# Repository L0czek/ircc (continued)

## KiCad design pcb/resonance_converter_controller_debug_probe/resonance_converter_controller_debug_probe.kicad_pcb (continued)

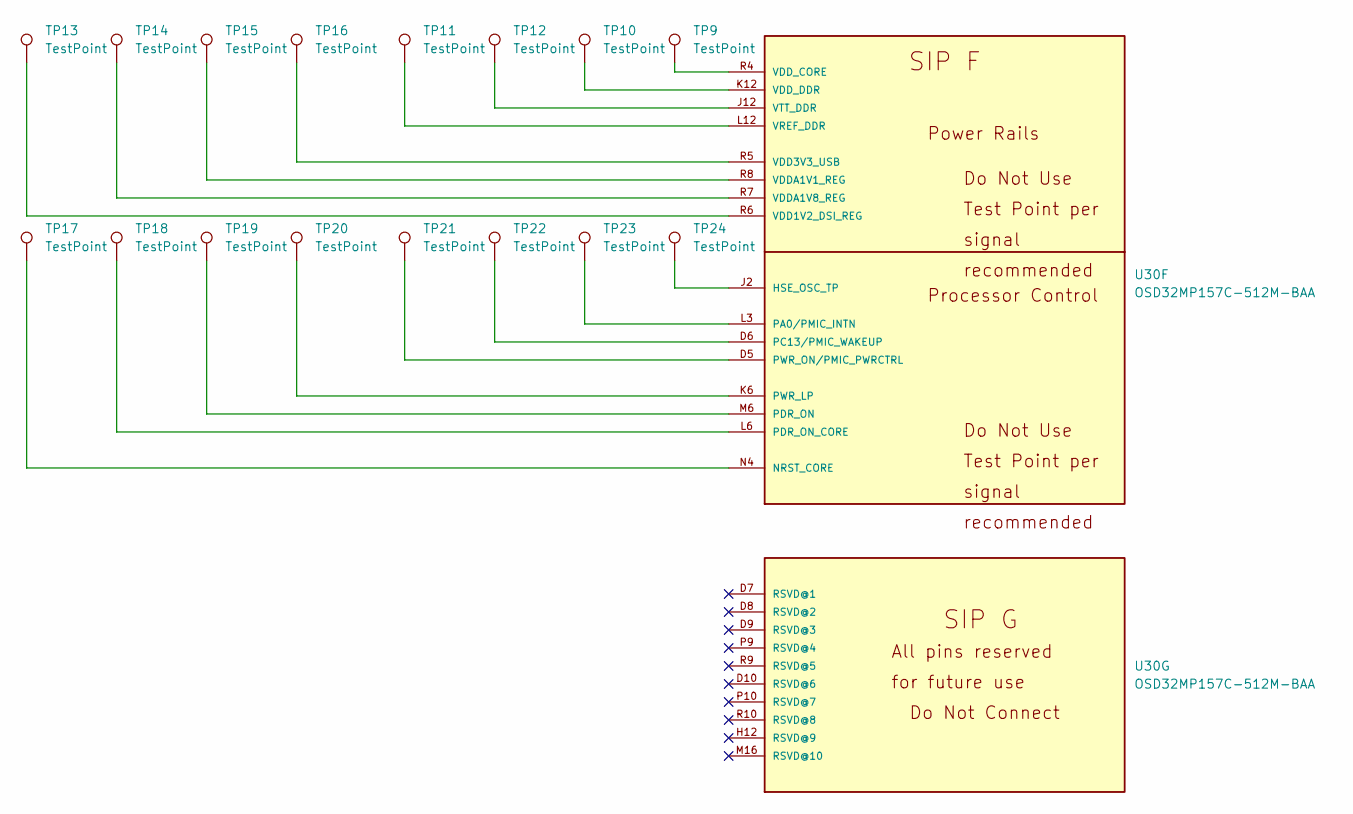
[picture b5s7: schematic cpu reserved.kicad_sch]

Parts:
TP9, TP10, TP11, TP12, TP13, TP14, TP15, TP16, TP17, TP18, TP19, TP20, TP21, TP22, TP23, TP24: TestPoint; TestPoint_Pad_D1.0mm
U30: OSD32MP157C-512M-BAA; OSD32MP15X-BGA-324

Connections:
unnamed: TP24.1, U30.J2 (HSE_OSC_TP)
unnamed: TP17.1, U30.N4 (NRST_CORE)
unnamed: TP23.1, U30.L3 (PA0/PMIC_INTN)
unnamed: TP22.1, U30.D6 (PC13/PMIC_WAKEUP)
unnamed: TP19.1, U30.M6 (PDR_ON)
unnamed: TP18.1, U30.L6 (PDR_ON_CORE)
unnamed: TP20.1, U30.K6 (PWR_LP)
unnamed: TP21.1, U30.D5 (PWR_ON/PMIC_PWRCTRL)
unnamed: TP13.1, U30.R6 (VDD1V2_DSI_REG)
unnamed: TP16.1, U30.R5 (VDD3V3_USB)
unnamed: TP15.1, U30.R8 (VDDA1V1_REG)
unnamed: TP14.1, U30.R7 (VDDA1V8_REG)
unnamed: TP9.1, U30.R4 (VDD_CORE)
unnamed: TP10.1, U30.K12 (VDD_DDR)
unnamed: TP11.1, U30.L12 (VREF_DDR)
unnamed: TP12.1, U30.J12 (VTT_DDR)

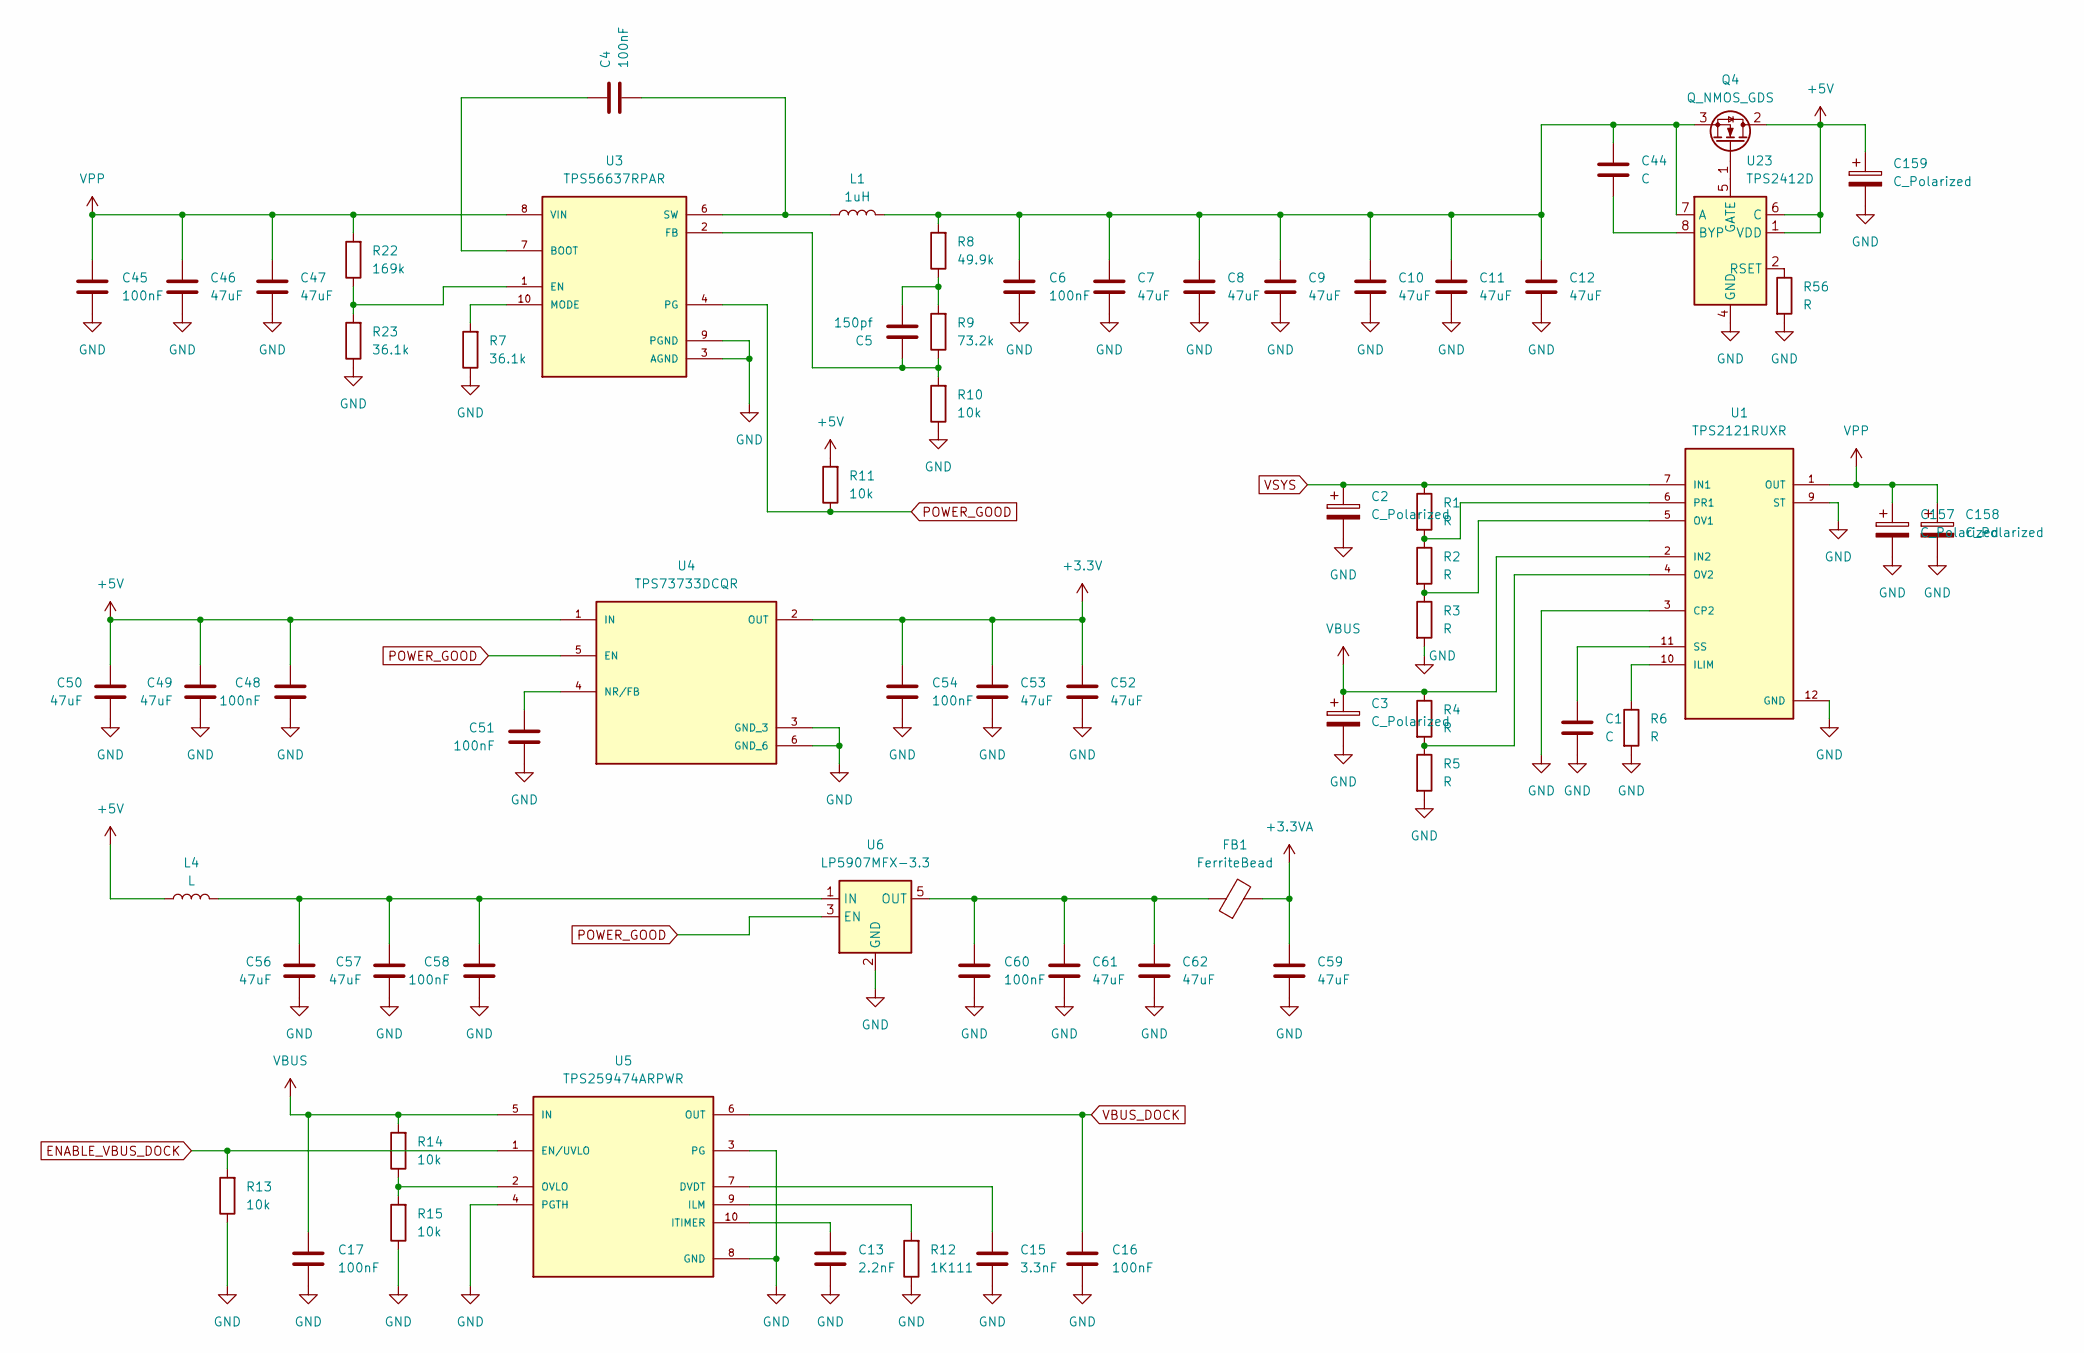
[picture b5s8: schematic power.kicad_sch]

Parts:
C1: C; C_0402_1005Metric
C2, C3, C157, C158, C159: C_Polarized; C_2220_5750Metric
C4, C6, C16, C17, C45, C48, C51, C54, C58, C60: 100nF; C_0402_1005Metric
C5: 150pf; C_0402_1005Metric
C7, C8, C9, C10, C11, C12, C46, C47, C49, C50, C52, C53, C56, C57, C59, C61, C62: 47uF; C_1206_3216Metric
C13: 2.2nF; C_0402_1005Metric
C15: 3.3nF; C_0402_1005Metric
C44: C; C_0805_2012Metric
FB1: FerriteBead; L_0805_2012Metric
L1: 1uH; L_10.4x10.4_H4.8
L4: L; L_1812_4532Metric
Q4: Q_NMOS_GDS; TO-252-2
R1, R2, R3, R4, R5, R6, R56: R; R_0402_1005Metric
R7, R23: 36.1k; R_0402_1005Metric
R8: 49.9k; R_0402_1005Metric
R9: 73.2k; R_0402_1005Metric
R10, R11, R13, R14, R15: 10k; R_0402_1005Metric
R12: 1K111; R_0402_1005Metric
R22: 169k; R_0402_1005Metric
U1: TPS2121RUXR; IC_TPS2121RUXR
U3: TPS56637RPAR; CONV_TPS56637RPAR; PARTREV A
U4: TPS73733DCQR; IC_TPS73733DCQR; PARTREV R
U5: TPS259474ARPWR; IC_TPS259474ARPWR; PARTREV A
U6: LP5907MFX-3.3; SOT-23-5
U23: TPS2412D; TSSOP-8_4.4x3mm_P0.65mm

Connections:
+3.3V: C52.1, C53.1, C54.1, U4.2 (OUT); also elsewhere on the board
+3.3VA: C59.1, FB1.2; also elsewhere on the board
+5V: C48.1, C49.1, C50.1, C159.1, L4.1, Q4.2 (D), R11.2, U4.1 (IN), U23.1 (VDD), U23.6 (C); also elsewhere on the board
ENABLE_VBUS_DOCK: R13.2, U5.1 (EN/UVLO)
GND: C1.2, C2.2, C3.2, C6.2, C7.2, C8.2, C9.2, C10.2, C11.2, C12.2, C13.2, C15.2, C16.2, C17.2, C45.2, C46.2, C47.2, C48.2, C49.2, C50.2, C51.2, C52.2, C53.2, C54.2, C56.2, C57.2, C58.2, C59.2, C60.2, C61.2, C62.2, C157.2, C158.2, C159.2, R3.2, R5.2, R6.2, R7.1, R10.1, R12.1, R13.1, R15.1, R23.1, R56.2, U1.3 (CP2), U1.9 (ST), U1.12 (GND), U3.3 (AGND), U3.9 (PGND), U4.3 (GND_3), U4.6 (GND_6), U5.3 (PG), U5.4 (PGTH), U5.8 (GND), U6.2 (GND), U23.3 (GND), U23.4 (GND); also elsewhere on the board
unnamed: C5.2, R8.1, R9.2
unnamed: Q4.1 (G), U23.5 (GATE)
unnamed: C6.1, C7.1, C8.1, C9.1, C10.1, C11.1, C12.1, C44.1, L1.2, Q4.3 (S), R8.2, U23.7 (A)
unnamed: R6.1, U1.10 (ILIM)
unnamed: R2.2, R3.1, U1.5 (OV1)
unnamed: R4.2, R5.1, U1.4 (OV2)
unnamed: R1.2, R2.1, U1.6 (PR1)
unnamed: C1.1, U1.11 (SS)
unnamed: C4.1, U3.7 (BOOT)
unnamed: R22.1, R23.2, U3.1 (EN)
unnamed: C5.1, R9.1, R10.2, U3.2 (FB)
unnamed: R7.2, U3.10 (MODE)
unnamed: C4.2, L1.1, U3.6 (SW)
unnamed: C51.1, U4.4 (NR/FB)
unnamed: C15.1, U5.7 (DVDT)
unnamed: R12.2, U5.9 (ILM)
unnamed: C13.1, U5.10 (ITIMER)
unnamed: R14.1, R15.2, U5.2 (OVLO)
unnamed: C56.1, C57.1, C58.1, L4.2, U6.1 (IN)
unnamed: C60.1, C61.1, C62.1, FB1.1, U6.5 (OUT)
unnamed: C44.2, U23.8 (BYP)
unnamed: R56.1, U23.2 (RSET)
POWER_GOOD: R11.1, U3.4 (PG), U4.5 (EN), U6.3 (EN)
VBUS: C3.1, C17.1, R4.1, R14.2, U1.2 (IN2), U1.2_1 (IN2), U5.5 (IN); also elsewhere on the board
VBUS_DOCK: C16.1, U5.6 (OUT); also elsewhere on the board
VPP: C45.1, C46.1, C47.1, C157.1, C158.1, R22.2, U1.1 (OUT), U1.1_1 (OUT), U1.8 (OUT), U1.8_1 (OUT), U3.8 (VIN)
VSYS: C2.1, R1.1, U1.7 (IN1), U1.7_1 (IN1); also elsewhere on the board

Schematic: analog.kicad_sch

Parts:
C30, C68, C69, C70, C71, C98, C103: 100nF; C_0402_1005Metric
D3, D7, D10, D11, D12, D13, D37: ESD9B3.3ST5G; D_SOD-923
R38, R43, R76, R78: 10K; R_0402_1005Metric
U9, U10, U11, U27: INA169; SOT-23-5
U12, U16: MCP4441-xxxx-ST; TSSOP-20_4.4x6.5mm_P0.65mm
U28: OPA356xxDBV; SOT-23-5

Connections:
+3.3V: C30.1, C103.1, U12.4 (HVC/A0), U12.15 (~RESET), U12.16 (A1), U12.17 (VDD), U16.4 (HVC/A0), U16.15 (~RESET), U16.16 (A1), U16.17 (VDD); also elsewhere on the board
+3.3VA: C68.2, C69.2, C70.2, C71.2, C98.1, U9.5 (V+), U10.5 (V+), U11.5 (V+), U27.5 (V+), U28.5 (V+); also elsewhere on the board
AUX_ADC: D3.2 (A2), R43.2; also elsewhere on the board
DAC_OUT: D37.2 (A2), R78.2; also elsewhere on the board
GND: C30.2, C68.1, C69.1, C70.1, C71.1, C98.2, C103.2, D3.1 (A1), D7.1 (A1), D10.1 (A1), D11.1 (A1), D12.1 (A1), D13.1 (A1), D37.1 (A1), R38.1, R43.1, R78.1, U9.2 (GND), U9.4 (-), U10.2 (GND), U10.4 (-), U11.2 (GND), U11.4 (-), U12.2 (P3W), U12.3 (P3B), U12.7 (VSS), U12.8 (P1B), U12.9 (P1W), U12.12 (P0W), U12.13 (P0B), U12.18 (P2B), U12.19 (P2W), U16.1 (P3A), U16.7 (VSS), U16.12 (P0W), U16.13 (P0B), U27.2 (GND), U27.4 (-), U28.2 (V-); also elsewhere on the board
I2C_INT_SCL: U12.5 (SCL), U16.5 (SCL); also elsewhere on the board
I2C_INT_SDA: U12.6 (SDA), U16.6 (SDA); also elsewhere on the board
ISENSE_1: D7.2 (A2), U9.3 (+); also elsewhere on the board
ISENSE_1_OUT: U9.1, U12.20 (P2A)
ISENSE_2: D10.2 (A2), U27.3 (+); also elsewhere on the board
ISENSE_2_OUT: U12.1 (P3A), U27.1
ISENSE_3: D11.2 (A2), U10.3 (+); also elsewhere on the board
ISENSE_3_OUT: U10.1, U12.10 (P1A)
ISENSE_4: D12.2 (A2), U11.3 (+); also elsewhere on the board
ISENSE_4_OUT: U11.1, U12.11 (P0A)
unnamed: R76.1, U16.11 (P0A), U28.4 (-)
VSENSE_IN: D13.2 (A2), R38.2, U28.3 (+); also elsewhere on the board
VSENSE_OUT: R76.2, U28.1

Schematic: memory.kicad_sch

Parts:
C105, C106, C108: 100nF; C_0402_1005Metric
C107: 10uF; C_1206_3216Metric
C109: 100uF; C_1206_3216Metric
J9, J10: Micro_SD_Card_Det2; microSD_HC_Hirose_DM3BT-DSF-PEJS
R67: 0R; R_0402_1005Metric; not fitted
R68: 240K; R_0402_1005Metric
R69: 100K; R_0402_1005Metric
U31: TPS2553DRVR; SON65P200X200X80-7N

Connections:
+3.3V: C105.1, R67.1, R69.2, U31.6 (IN); also elsewhere on the board
GND: C105.2, C106.2, C107.2, C108.2, C109.2, J9.6 (VSS), J9.10 (DET_A), J9.11 (SHIELD), J10.6 (VSS), J10.10 (DET_A), J10.11 (SHIELD), R68.2, U31.5 (GND), U31.7 (EP); also elsewhere on the board
unnamed: C107.1, C108.1, C109.1, J9.4 (VDD), J10.4 (VDD), U31.1 (OUT)
unnamed: C106.1, R69.1, U31.3 (~FAULT), U31.4 (EN)
unnamed: R67.2, R68.1, U31.2 (ILIM)
SD0_CLK: J9.5 (CLK); also elsewhere on the board
SD0_CMD: J9.3 (CMD); also elsewhere on the board
SD0_D0: J9.7 (DAT0); also elsewhere on the board
SD0_D1: J9.8 (DAT1); also elsewhere on the board
SD0_D2: J9.1 (DAT2); also elsewhere on the board
SD0_D3: J9.2 (DAT3/CD); also elsewhere on the board
SD0_DET: J9.9 (DET_B)
SD1_CLK: J10.5 (CLK); also elsewhere on the board
SD1_CMD: J10.3 (CMD); also elsewhere on the board
SD1_D0: J10.7 (DAT0); also elsewhere on the board
SD1_D1: J10.8 (DAT1); also elsewhere on the board
SD1_D2: J10.1 (DAT2); also elsewhere on the board
SD1_D3: J10.2 (DAT3/CD); also elsewhere on the board
SD1_DET: J10.9 (DET_B)

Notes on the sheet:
3.3 bus max 100mA

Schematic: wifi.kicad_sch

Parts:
C110: C_Polarized; CP_EIA-7343-31_Kemet-D
H1: MountingHole_Pad; screw-stud
J11: Bus_M.2_Socket_E; MDTXXXXXX001
R64, R65, R70: 10k; R_0402_1005Metric
R66, R71: 0R; R_0402_1005Metric; not fitted

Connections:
+1V8: R64.1, R65.1; also elsewhere on the board
+3.3V: C110.1, J11.2 (3.3V), J11.4 (3.3V), J11.72 (3.3V), J11.74 (3.3V), R70.1; also elsewhere on the board
BLE_ENABLE: J11.54 (~W_DISABLE2)
BLE_UART_CTS: J11.34 (UART_CTS); also elsewhere on the board
BLE_UART_RTS: J11.36 (UART_RTS); also elsewhere on the board
BLE_UART_RXD: J11.22 (UART_RXD); also elsewhere on the board
BLE_UART_TXD: J11.32 (UART_TXD); also elsewhere on the board
BLE_UART_WAKE: J11.20 (~UART_WAKE), R70.2, R71.2
GND: C110.2, H1.1 (1_1), J11.1 (GND), J11.7 (GND), J11.18 (GND), J11.33 (GND), J11.39 (GND), J11.45 (GND), J11.51 (GND), J11.57 (GND), J11.63 (GND), J11.69 (GND), J11.75 (GND), J11.S1 (GND), J11.S2 (GND); also elsewhere on the board
unnamed: J11.40 (VENDOR_DEFINED), R66.1
unnamed: J11.42 (VENDOR_DEFINED), R71.1
WIFI_ENABLE: J11.56 (~W_DISABLE1)
WIFI_SDIO_CLK: J11.9 (SDIO_CLK); also elsewhere on the board
WIFI_SDIO_CMD: J11.11 (SDIO_CMD); also elsewhere on the board
WIFI_SDIO_D0: J11.13 (SDIO_DATA0); also elsewhere on the board
WIFI_SDIO_D1: J11.15 (SDIO_DATA1); also elsewhere on the board
WIFI_SDIO_D2: J11.17 (SDIO_DATA2); also elsewhere on the board
WIFI_SDIO_D3: J11.19 (SDIO_DATA3); also elsewhere on the board
WIFI_SDIO_RESET: J11.23 (~SDIO_RESET), R65.2
WIFI_SDIO_WAKE: J11.21 (~SDIO_WAKE), R64.2, R66.2
WIFI_SUSCLK: J11.50 (SUSCLK)

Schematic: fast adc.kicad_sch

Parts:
C18, C19, C24, C25, C26, C27, C28, C29, C139, C140, C141, C143, C144: 100nF; C_0402_1005Metric
C20, C21, C22, C23: 10uF; C_1206_3216Metric
C142, C145, C146, C147, C148: 10u; C_0805_2012Metric
D1, D2: ESD9B3.3ST5G; D_SOD-923
L2: L; L_0805_2012Metric
R16, R17, R18, R19, R20, R21, R24, R25, R26, R29, R30, R33, R34, R35, R36, R37, R39, R40: 10K; R_0402_1005Metric
R27, R28, R41, R42: 10R; R_0402_1005Metric
R72: 10k; R_0402_1005Metric
U7: ADC3910D125IRSMT; IC_ADC3910D125IRSMT; PARTREV A
U8, U14: OPA333xxDBV; SOT-23-5
U13, U15: THS4541IRGTT; QFN50P300X300X100-17N
U16: MCP4441-xxxx-ST; TSSOP-20_4.4x6.5mm_P0.65mm
U33: LP5912-1.8DRV; WSON-6-1EP_2x2mm_P0.65mm_EP1x1.6mm_ThermalVias

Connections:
1V8A: C28.1, C29.1, C147.1, C148.1, L2.2, U7.12 (AVDD), U7.13 (AVDD)
+3.3V: C139.1, U7.27 (IOVDD); also elsewhere on the board
+3.3VA: C26.1, C27.1, C140.1, C141.1, C142.1, C143.1, R26.1, R30.1, U8.5 (V+), U13.5 (VS+-2), U13.6 (VS+-3), U13.7 (VS+), U13.8 (VS+-1), U13.12 (PDN), U14.5 (V+), U15.5 (VS+-2), U15.6 (VS+-3), U15.7 (VS+), U15.8 (VS+-1), U15.12 (PDN), U33.4 (EN), U33.6 (IN); also elsewhere on the board
ADC_ALERT: U7.20 (ALERT)
ADC_CLK: U7.8 (CLK)
ADC_D0: U7.4 (D0); also elsewhere on the board
ADC_D1: U7.3 (D1); also elsewhere on the board
ADC_D2: U7.2 (D2); also elsewhere on the board
ADC_D3: U7.1 (D3); also elsewhere on the board
ADC_D4: U7.32 (D4); also elsewhere on the board
ADC_D5: U7.31 (D5); also elsewhere on the board
ADC_D6: U7.26 (D6); also elsewhere on the board
ADC_D7: U7.25 (D7); also elsewhere on the board
ADC_D8: U7.24 (D8); also elsewhere on the board
ADC_D9: U7.23 (D9); also elsewhere on the board
ADC_D10: U7.22 (D10); also elsewhere on the board
ADC_D11: U7.21 (D11); also elsewhere on the board
ADC_DCLK: U7.30 (DCLK); also elsewhere on the board
ADC_OEN: U7.6 (~OEN/PD)
ADC_RESET: U7.9 (RESET)
ADC_SCLK: U7.18 (SCLK); also elsewhere on the board
ADC_SDIO: U7.19 (SDIO); also elsewhere on the board
ADC_SS: U7.16 (~SEN); also elsewhere on the board
GND: C18.1, C21.1, C22.1, C24.1, C26.2, C27.2, C28.2, C29.2, C139.2, C140.2, C141.2, C142.2, C143.2, C144.2, C145.2, C146.2, C147.2, C148.2, D1.1 (A1), D2.1 (A1), R24.1, R25.2, R29.1, R33.2, U7.17 (VREF), U7.28 (DGND), U7.33 (GND), U8.2 (V-), U13.13 (VS--2), U13.14 (VS--3), U13.15 (VS-), U13.16 (VS--1), U14.2 (V-), U15.13 (VS--2), U15.14 (VS--3), U15.15 (VS-), U15.16 (VS--1), U33.5 (GND), U33.7 (EP); also elsewhere on the board
unnamed: C18.2, R17.2
unnamed: C19.1, R18.2
unnamed: C19.2, R21.1, U8.1
unnamed: C20.1, R20.2
unnamed: C23.1, R34.2
unnamed: C24.2, R36.2
unnamed: C25.1, R37.2
unnamed: C25.2, R35.1, U14.1
unnamed: R28.1, U7.11 (INAM)
unnamed: R27.1, U7.10 (INAP)
unnamed: R42.1, U7.15 (INBM/NC)
unnamed: R41.1, U7.14 (INBP/NC)
unnamed: C21.2, R25.1, R26.2, U8.3 (+)
unnamed: R19.1, U13.4 (FB+)
unnamed: R16.1, U13.1 (FB-)
unnamed: R16.2, R17.1, U13.2 (IN+)
unnamed: R18.1, R19.2, U13.3 (IN-)
unnamed: R27.2, U13.10 (OUT+)
unnamed: R28.2, U13.11 (OUT-)
unnamed: C22.2, R30.2, R33.1, U14.3 (+)
unnamed: U14.4 (-), U16.19 (P2W)
unnamed: R40.1, U15.4 (FB+)
unnamed: R39.1, U15.1 (FB-)
unnamed: R36.1, R39.2, U15.2 (IN+)
unnamed: R37.1, R40.2, U15.3 (IN-)
unnamed: R41.2, U15.10 (OUT+)
unnamed: R42.2, U15.11 (OUT-)
unnamed: R20.1, U16.10 (P1A)
unnamed: R21.2, U16.8 (P1B)
unnamed: U8.4 (-), U16.9 (P1W)
unnamed: R34.1, U16.20 (P2A)
unnamed: R35.2, U16.18 (P2B)
unnamed: C144.1, C145.1, C146.1, L2.1, R72.1, U33.1 (OUT)
unnamed: R72.2, U33.3 (PG)
OCD2_IN: C23.2, D2.2 (A2), R29.2; also elsewhere on the board
OCD_IN: C20.2, D1.2 (A2), R24.2; also elsewhere on the board
VOCM: U7.7 (VCM), U13.9 (VOCM), U15.9 (VOCM)

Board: 4 copper layers, 310 parts (62 on the bottom side), 264 nets, no tracks yet.
